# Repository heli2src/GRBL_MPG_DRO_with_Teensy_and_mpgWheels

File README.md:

# GRBL_MPG_DRO_with_Teensy_and_MPG_Wheels

Control of the grpHall with a small touch display (ILI9341 320x240) and mpg-wheels connected via RS485.
\
The main aim was to be able to continue using both the lathe and the milling machine 'manually'. Manual only means that they should work as before. In other words, to move a rotary wheel around an axis. 
Especially when turning, you often just want to machine a part quickly, which is often faster conventionally than laboriously writing and testing the first G-code.
But if you equip your machine with stepper motors or servomotors, then of course it should also be possible to process G-code. That's why pure cycle electronics were out of the question for me.
\
This Project is starting from [GRBL_MPG_DRO_BoosterPack](https://github.com/terjeio/GRBL_MPG_DRO_BoosterPack).
But is use a [Teensy 3.2](https://www.pjrc.com/store/teensy32.html) for controlling. The big difference 
is that you can not only use 2 MPG wheels, but several, which can also be distributed on the machine.
The MPG wheels are connected via an rs485 busconnection.
\
\
The canvas structure from Terjeio project was unfortunately difficult for me to understand and extend (I'm not such a C pro), so I didn't use it and built my own structure. In particular, I like to use Kris Kasprzak [libraries](https://github.com/KrisKasprzak?tab=repositories), which in my opinion allow you to realize displays and buttons quite quickly and easily. But the mixture of the whole thing was not so easy, so that the whole code is again more difficult to understand :-(
\
\
The requirement is that the [grbHAL driver](https://github.com/grblHAL) is used as the CNC controller. The UART input is then used to communicate with the display and the MPGs. I use the [grbl-teensy-4](https://github.com/phil-barrett/grblHAL-teensy-4.x) board to control the motors and the connections of the inputs and outputs.  You cannot use USB and Uart at the same time with this board. USB is therefore switched off. If you want to run CNC programs, you have to connect the board to your network via Ethernet. I then use the [IoSender](https://github.com/terjeio/ioSender) as user interface.
\
The display can be used as a pure display when processing CNC code (sent via ioSender) or as a display and control unit when controlling the milling machine or lathe manually. Switching is done with a button on the display. An LED indicates the current mode.
\
\
There is still some tidying up to be done, but certain extensions are even more important at the moment for proper working.
The Source code not ready yet, there could be bugs, use it carfully!
\
\
Features from the current version:
- Control board with a SPI LCD and touch interface (ILI9341 320x240), connect via Uart with the [grbHAL driver](https://github.com/grblHAL).
- each MPG wheels has its own [Pi Pico](https://www.raspberrypi.com/products/raspberry-pi-pico/) connected via rs485 with the control board.
  Own control switches and a small display is possible (SSD1306 or SH1106 (128x64) via I2C).
- Switching from pure DRO for external CNC code and manual operation with the handwheels, and simple cycles such as turning cones or any thread.
- DRO/MPG display actual and target values.
- Support 3D milling machine X,Y,Z Feed Rate with mm/min, or lathe X,Z Feedrate mm/min when the machine is stopped, and mm/U when the machine is turning.
- More axis travel via the screen.
- Home driving
- reset/unlock Aarms
- MPG-Wheel features:
  - Setting for the wheel wheel and the buttons set, axis, rotate screen/bars.
  - Move 1-axis with the rotary wheel.
  - Setting the resolution of the wheel via button for each axis, 0.01/0.1/1 mm.
  - Set display value to 0 for each axis.
  - Use the button to quickly return to 0.
  - Drive to the target point at the set feed rate using a button.
  - Drive to a target point with the rotary wheel, then quickly return with the pushbutton and drive back to the last target point at the set feed rate --> Simple cycling with manual adjustment of another axis.
- DRO set to 0 for 
\
# planned
- lathe : 
  - thread cutting
  - Turn cone
  - Run cycles
- Milling: 
  - mill surface flat
  - Milling pools
\
### Todo
- The rotational speed of the wheels is not yet properly evaluated. As a result, the whole thing still runs a little rough.
- Simultaneous driving of 2-axes over the wheels does not yet work in practice.
- The entire software is still under construction, which is why there is no release yet.
\
\
Here I have converted my lathe, a Quantum D240x400E.
With the wheels you can also use the machine conventionally. In some cases, you can also drive certain cycles very easily. However, this has only been implemented in a rudimentary way so far.
</img>
\
\
\
## Compiling

### - Teensy for the touch display

With the Arduino version 2.3.6 you should be able to compile without errors.

Following libs are used:

- https://github.com/KrisKasprzak/FlickerFreePrint
- https://github.com/KrisKasprzak/ILI9341_t3_controls
- https://github.com/KrisKasprzak/ILI9341_t3_Menu
- https://github.com/ardnew/XPT2046_Calibrated
- [Bugtton](https://github.com/sakabug/Bugtton)      Version 1.0.5
- [MicroDebug](https://github.com/rlogiacco/MicroDebug)   Version 1.1

### - Raspi pico for the mpg wheels

- download the latest micropython version from  https://micropython.org/download/RPI_PICO/.
- Hold down the BOOTSEL button while plugging the board into USB.
  The uf2 file should then be copied to the USB mass storage device that appears.
- Copy the files src\mpg_wheel\RP2040 with the Thonny IDE (https://thonny.org/) to your raspi pico.
- or you can use https://docs.micropython.org/en/latest/reference/mpremote.html 
- rename 'display_cnc_achse.py' to 'main.py' on the raspi pico

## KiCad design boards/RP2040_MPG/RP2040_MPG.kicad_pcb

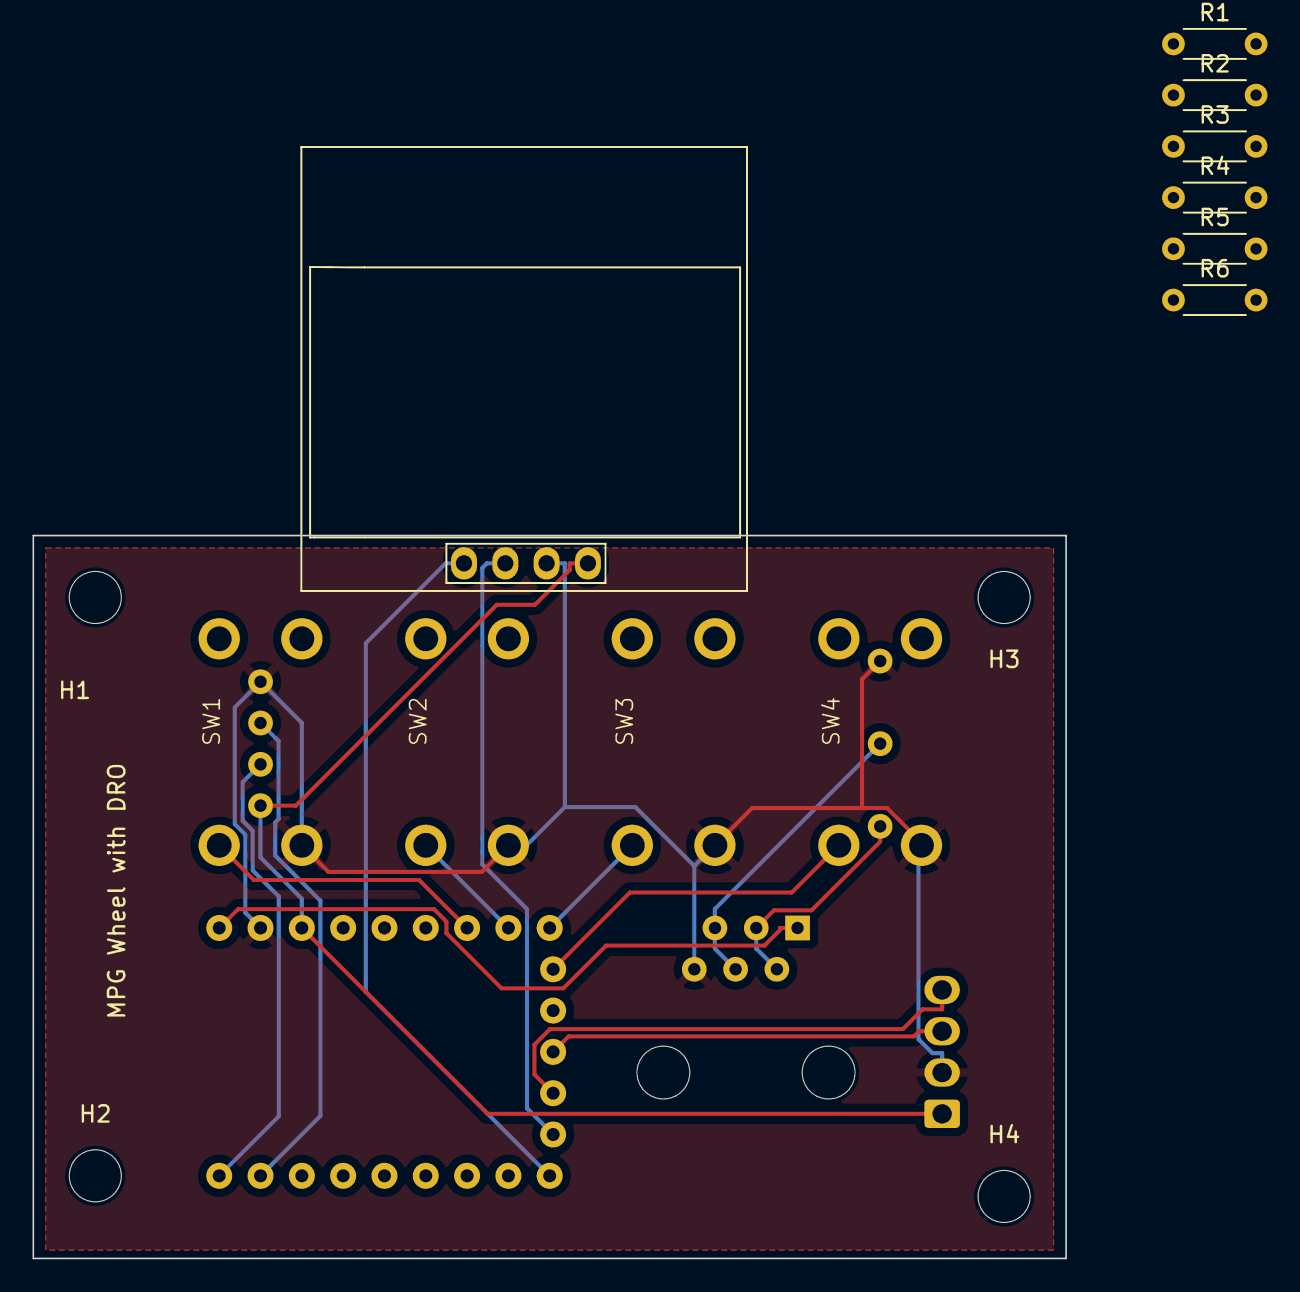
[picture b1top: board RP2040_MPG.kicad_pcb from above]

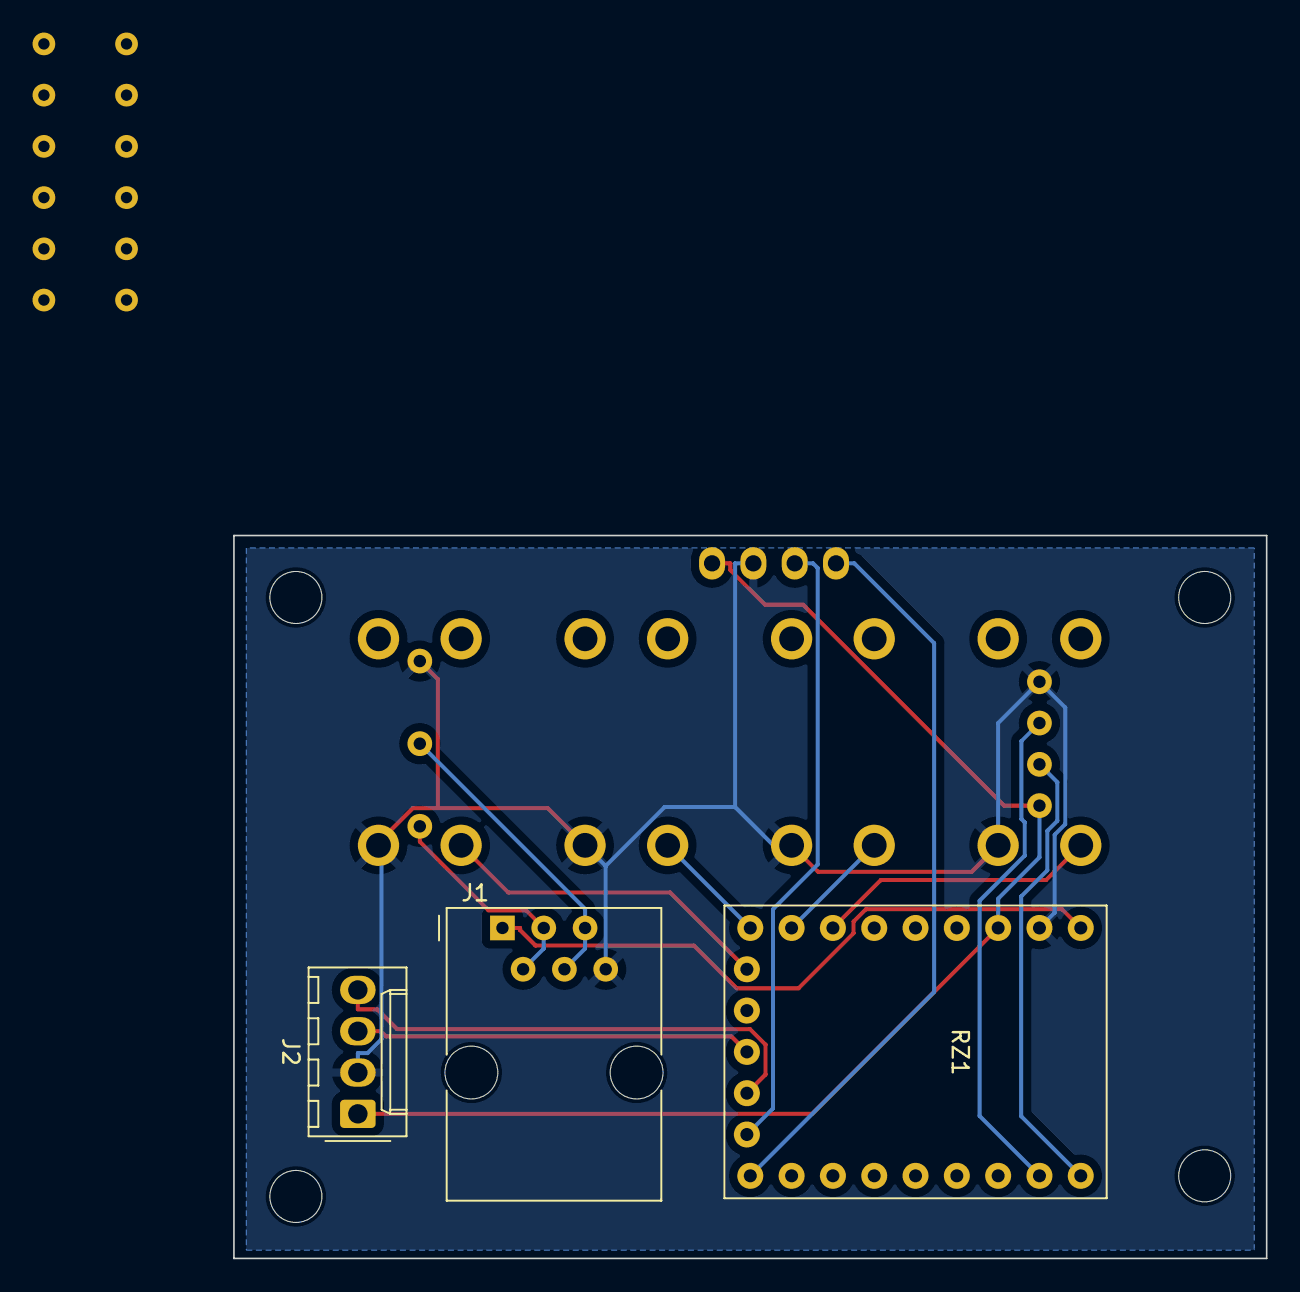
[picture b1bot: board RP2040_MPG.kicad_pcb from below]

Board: 2 copper layers, 63.5 x 44.5 mm, 19 parts (4 on the bottom side), 21 nets.

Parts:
Brd1: SSD1306; 128x64OLED
H1, H2, H3, H4: MountingHole; MountingHole_3.2mm_M3_DIN965
J1: RJ12; RJ12_Amphenol_54601
J2: Conn_01x04_Socket; Molex_KK-254_AE-6410-04A_1x04_P2.54mm_Vertical
R1, R2, R3, R4, R5, R6: 4k7; R_Axial_DIN0204_L3.6mm_D1.6mm_P5.08mm_Horizontal
RZ1: RP2040-Zero
SW1, SW2, SW3, SW4: SW_Push; Drucktaster_12x12
U2: RS485_2_TTL_UART

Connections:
GND: Brd1.2 (GND), J1.6, J2.2, RZ1.23 (GND), SW1.2, SW2.2, SW3.2, SW4.2, U2.4 (GND), U2.7 (Y)
unnamed: Brd1.3 (SCL), RZ1.10 (GP9)
unnamed: Brd1.4 (SDA), RZ1.9 (GP8)
unnamed: Brd1.1 (VCC), RZ1.21 (3V3), U2.1 (VCC)
unnamed: R1.2, SW4.1
unnamed: R2.2, SW3.1
unnamed: R3.2, SW2.1
unnamed: R4.2, SW1.1
unnamed: J1.1, J2.1, RZ1.22 (5V)
unnamed: J2.3, R6.2
unnamed: J2.4, R5.2
unnamed: RZ1.1 (GP0), U2.2 (TXD)
unnamed: RZ1.2 (GP1), U2.3 (RXD)
unnamed: R5.1, RZ1.11 (GP10)
unnamed: R6.1, RZ1.12 (GP11)
unnamed: R1.1, RZ1.14 (GP13)
unnamed: R2.1, RZ1.15 (GP14)
unnamed: R3.1, RZ1.16 (GP15)
unnamed: R4.1, RZ1.17 (GP26)
unnamed: J1.2, J1.3, U2.5 (A+)
unnamed: J1.4, J1.5, U2.6 (B-)

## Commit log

2023-02-25 first intermediate Version, but some work necessary
2023-02-25 add manuals and images
2023-02-25 add mpg wheel
2023-02-26 rename filename
2023-04-12 remove backups
2023-04-12 add title
2023-06-25 add comment
2023-06-25 fix compile error
2023-06-25 add colours
2023-06-25 rename timeout -> timeout_time
2023-06-25 change comments
2023-06-25 fix wrong increment
2023-06-25 add notFound if display not available
2023-06-25 remove read error
2023-06-25 add fp-info-cache to ignore list
2023-06-25 add ssd dummy
2023-06-27 add Fz with mm/min
2023-06-27 add spec for wheel
2023-06-27 store error and alarm codes in extra file
2023-06-27 WIP add fzmin
2023-06-28 change variable name
2023-06-28 add debug informationn about eeprom
2023-06-28 change variable name, for a better meaning
2023-06-28 rm unnecessary code, add comment
2023-06-29 fix error
2023-06-29 store unused function in joystick.h
2023-06-29 move validation from keys to the dedicated function from the pages
2023-07-02 add debouncing
2023-07-02 add eeprom values
2023-07-02 default values for fzjog commands
2023-07-02 fix wrong cnt values, if handwheel get an reset
2023-07-02 fix error with alarm/error state with new code structure
2023-07-02 add osci pictures from mpg wheel with different voltages
2023-07-04 add class for the rgb led from pico zero
2023-07-04 add WDT and ws2812
2023-07-05 add type of display
2023-07-13 fix listen slaveadress
2023-07-16 remove unnecessary variable and code
2023-07-16 add a-axis
2023-07-16 try to read more axes
2023-07-17 fix more axis
2023-07-17 fix error in axis, comment debug prints
2023-07-26 add RC vor switches and MPG
2023-07-26 create bracket for lcd-display
2023-08-06 add used libraries
2023-08-06 fix compiler error
2023-08-08 add 2 switch buttons
2023-08-08 add libs for compiling
2023-08-10 increase cycletime for mpg wheel
2023-08-10 use arduino 1.8.19 for compiling
2023-08-13 add mirrored switch layout
2023-08-13 improve timing
2023-08-13 add key functions from mpg-wheel
2023-08-19 add invers rotary
2023-08-26 add drive axis =0 and replace target value with actual value
2023-09-03 change x-pos
2023-09-03 fix unformated error display
2023-09-03 change display drehen
2023-09-03 fix error if rotary is inverted
2023-09-03 change some comments
2023-09-03 change rc filter
2023-10-13 add a test-file for the display
2023-10-13 change display format
2024-04-20 move modules to lib directory
2024-04-21 add setup page
2024-07-21 add switch beetwenn lathe/milling
2024-07-22 add manual calibration touch screen
2024-07-23 add 4xswitches
2024-07-23 add emv circuits
2024-07-23 improve readme and add pictures/cad drawings
2024-07-23 add changing axis with buttons
2024-10-06 comment
2024-10-12 add switching between CNC-Mode and manual mode
2025-05-06 replace SSD1306oled with SH1106
2025-05-17 update code for arduino 2.3 compilation
2025-05-26 fix 2d/3d driving
2025-05-28 fix button mpg-Button not functional...
2025-05-28 add display feed rate in milling mode
2025-05-28 add macro for pocket milling
